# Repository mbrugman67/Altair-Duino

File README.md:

# Altair-Duino projects
This is the central repo for my Altair-Duino projects.

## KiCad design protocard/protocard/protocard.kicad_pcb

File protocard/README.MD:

# Protocard
KiCAD files for a prototyping bus expansion card for the Altair-Duino 8800 Experimenter

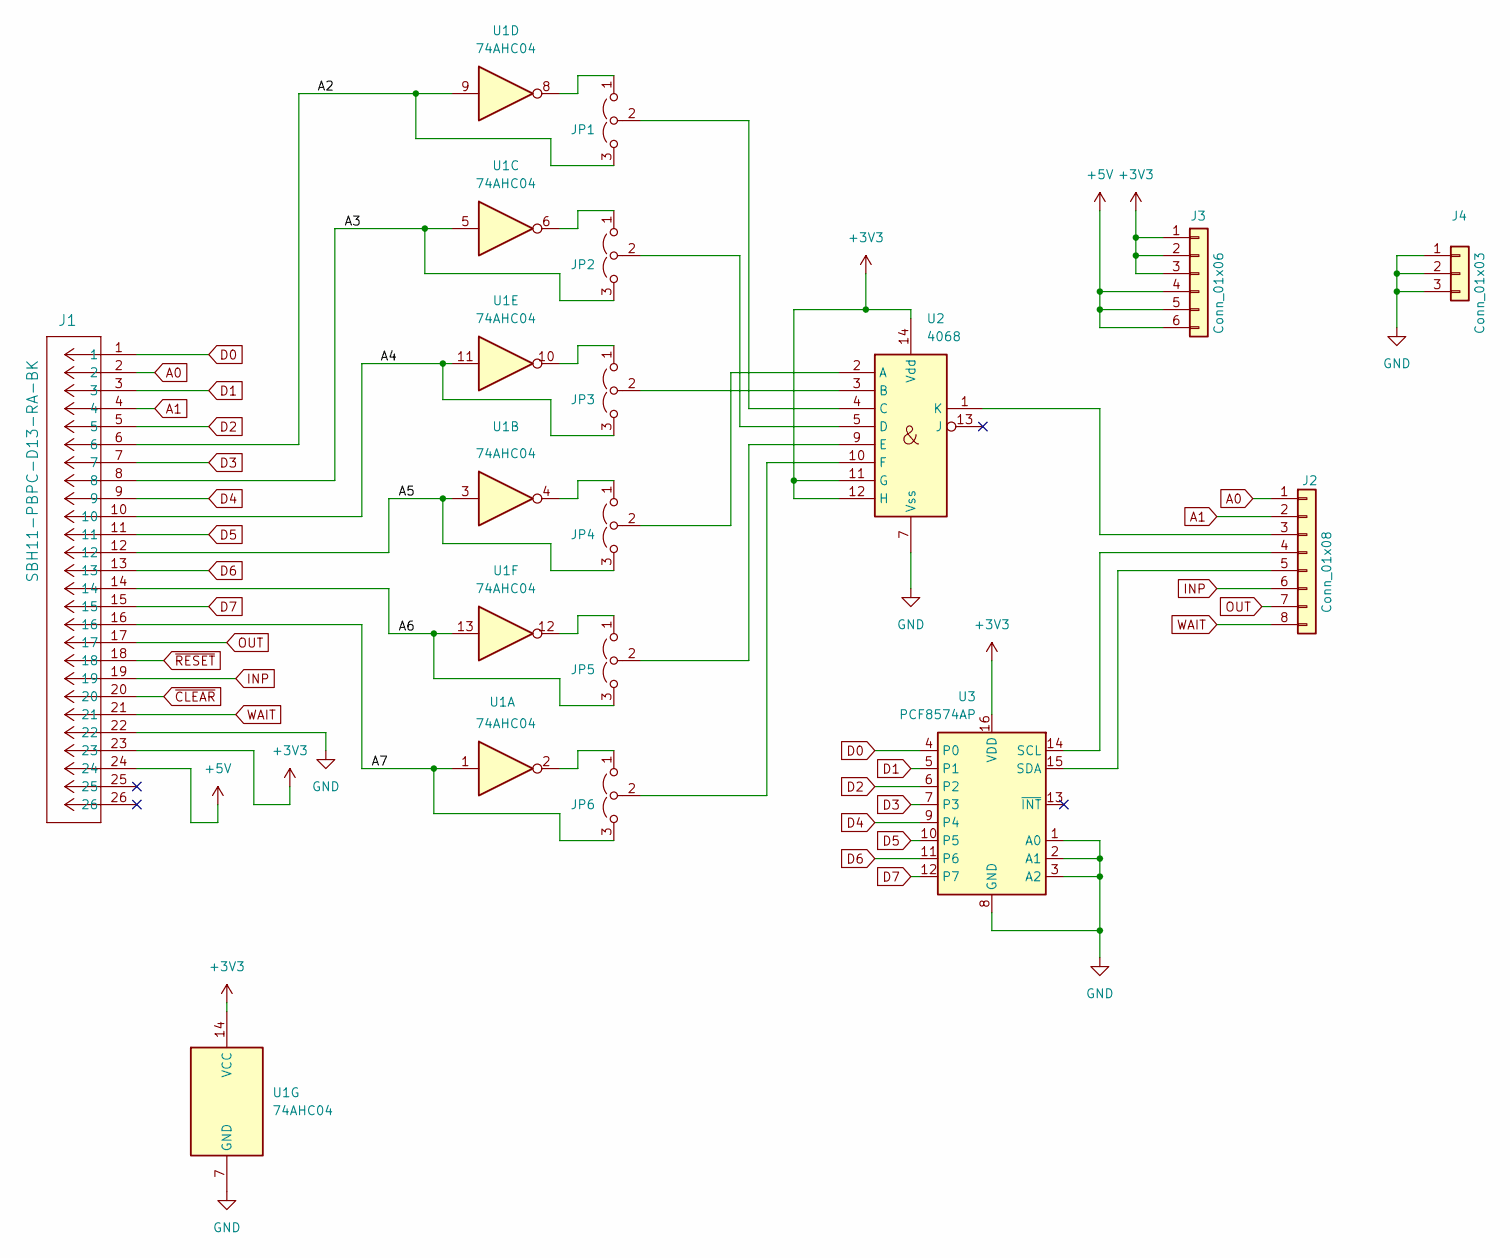
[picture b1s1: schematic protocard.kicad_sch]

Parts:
J1: SBH11-PBPC-D13-RA-BK; CONN_SBH11-PBPC-D13-RA-BK_SUL
J2: Conn_01x08; PinHeader_1x08_P2.54mm_Vertical
J3: Conn_01x06; PinHeader_1x06_P2.54mm_Vertical
J4: Conn_01x03; PinHeader_1x03_P2.54mm_Vertical
JP1, JP2, JP3, JP4, JP5, JP6: Jumper_3_Open; PinHeader_1x03_P2.54mm_Vertical
U1: 74AHC04; DIP-14_W7.62mm_Socket
U2: 4068; DIP-14_W7.62mm_Socket
U3: PCF8574AP; DIP-16_W7.62mm

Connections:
+3V3: J1.23, J3.1, J3.2, J3.3, U1.14 (VCC), U2.11 (G), U2.12 (H), U2.14 (Vdd), U3.16 (VDD)
+5V: J1.24, J3.4, J3.5, J3.6
/A2: J1.6, JP1.3 (B), U1.9
/A3: J1.8, JP2.3 (B), U1.5
/A4: J1.10, JP3.3 (B), U1.11
/A5: J1.12, JP4.3 (B), U1.3
/A6: J1.14, JP5.3 (B), U1.13
/A7: J1.16, JP6.3 (B), U1.1
A0: J1.2, J2.1
A1: J1.4, J2.2
D0: J1.1, U3.4 (P0)
D1: J1.3, U3.5 (P1)
D2: J1.5, U3.6 (P2)
D3: J1.7, U3.7 (P3)
D4: J1.9, U3.9 (P4)
D5: J1.11, U3.10 (P5)
D6: J1.13, U3.11 (P6)
D7: J1.15, U3.12 (P7)
GND: J1.22, J4.1, J4.2, J4.3, U1.7 (GND), U2.7 (Vss), U3.1 (A0), U3.2 (A1), U3.3 (A2), U3.8 (GND)
INP: J1.19, J2.6
unnamed: J2.3, U2.1 (K)
unnamed: J2.4, U3.14 (SCL)
unnamed: J2.5, U3.15 (SDA)
unnamed: JP1.1 (A), U1.8
unnamed: JP1.2 (C), U2.4 (C)
unnamed: JP2.1 (A), U1.6
unnamed: JP2.2 (C), U2.5 (D)
unnamed: JP3.1 (A), U1.10
unnamed: JP3.2 (C), U2.3 (B)
unnamed: JP4.1 (A), U1.4
unnamed: JP4.2 (C), U2.2 (A)
unnamed: JP5.1 (A), U1.12
unnamed: JP5.2 (C), U2.9 (E)
unnamed: JP6.1 (A), U1.2
unnamed: JP6.2 (C), U2.10 (F)
OUT: J1.17, J2.7
WAIT: J1.21, J2.8
~CLEAR: J1.20
~RESET: J1.18

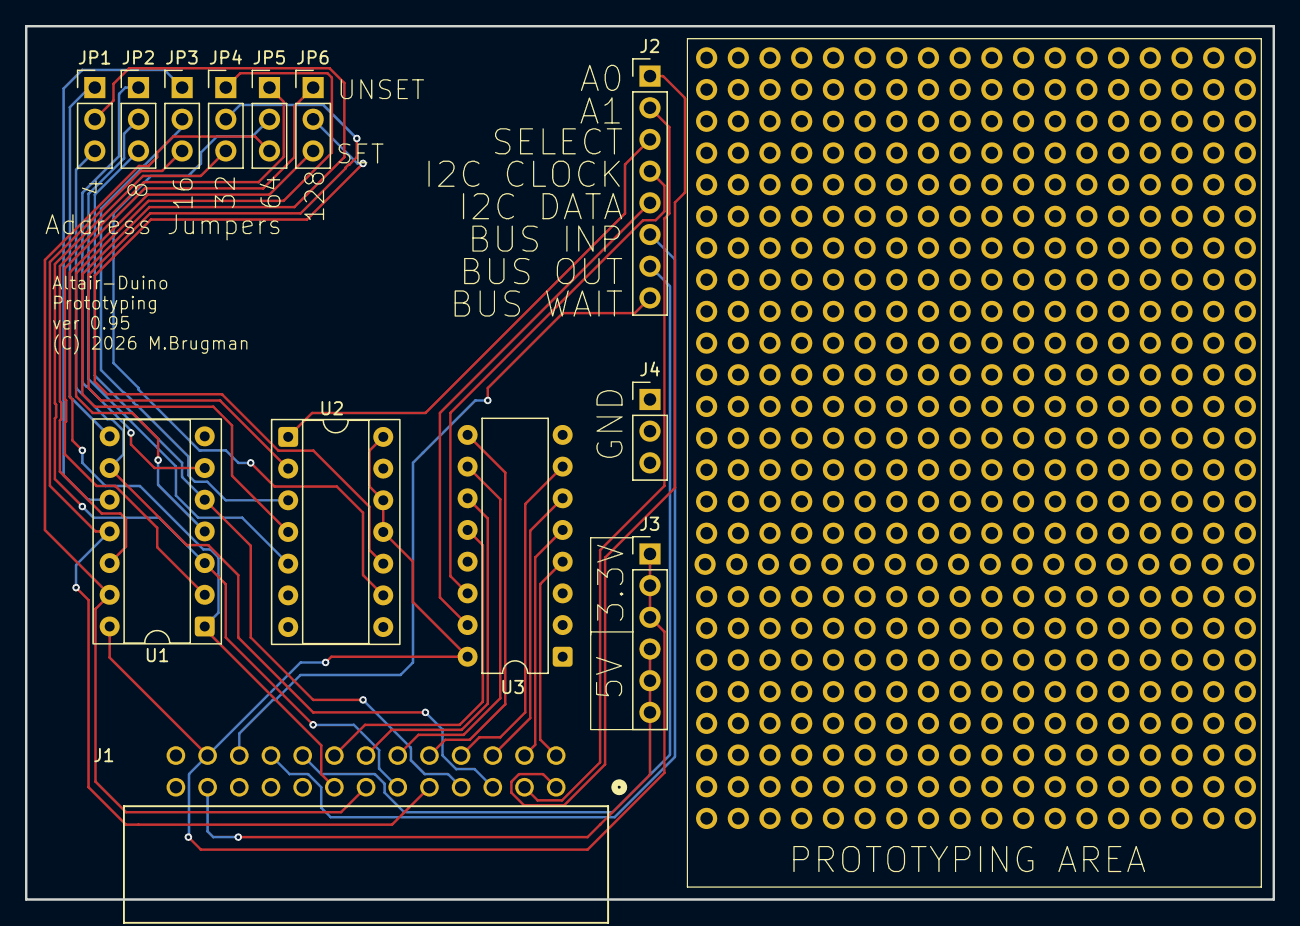
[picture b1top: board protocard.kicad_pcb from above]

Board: 2 copper layers, 100.0 x 70.0 mm, 13 parts (0 on the bottom side), 37 nets.

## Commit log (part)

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2026-02-26 Initial
2026-03-01 some fixes
2026-03-11 adding protoboard KiCAD files
2026-03-11 adding images of protocard
2026-03-31 adding assembly, fixes to PCB

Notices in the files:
protocard/protocard/protocard.kicad_pcb:
(C) 2026 M.Brugman
